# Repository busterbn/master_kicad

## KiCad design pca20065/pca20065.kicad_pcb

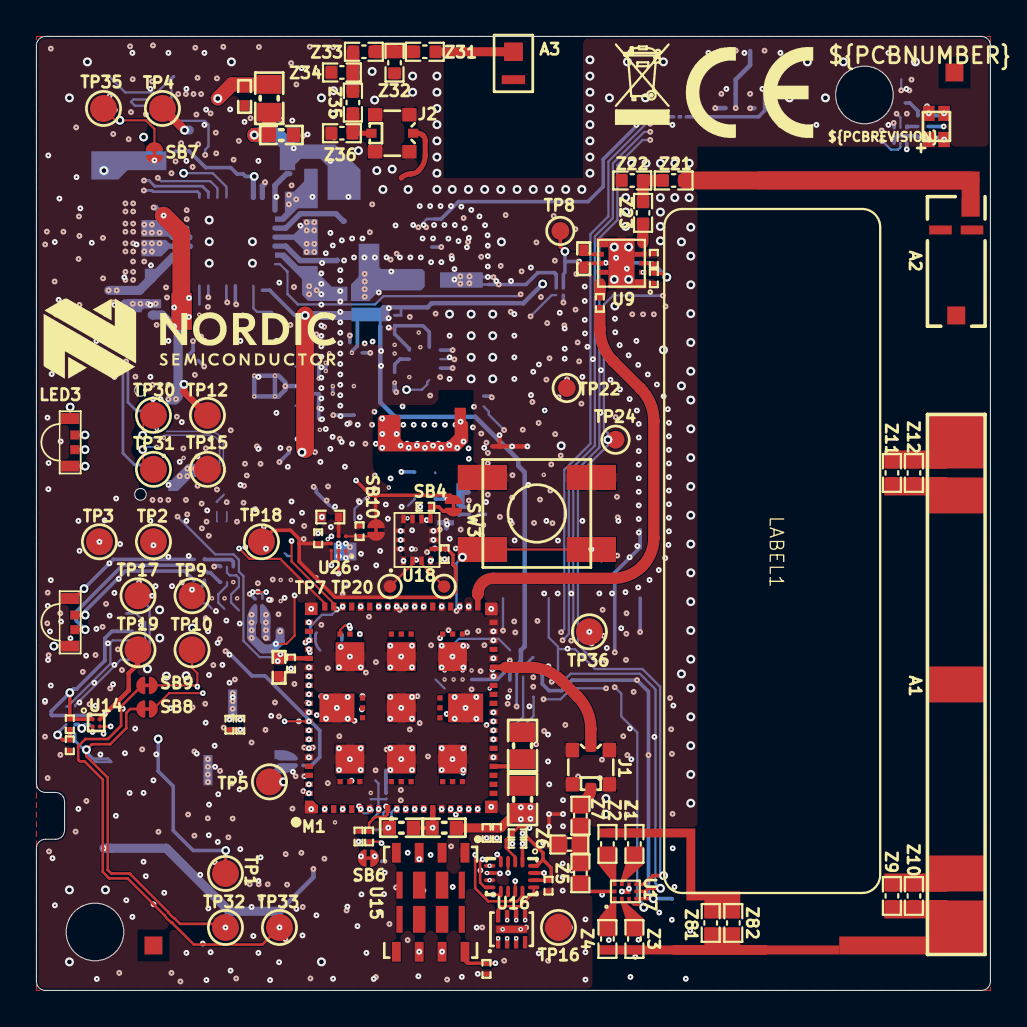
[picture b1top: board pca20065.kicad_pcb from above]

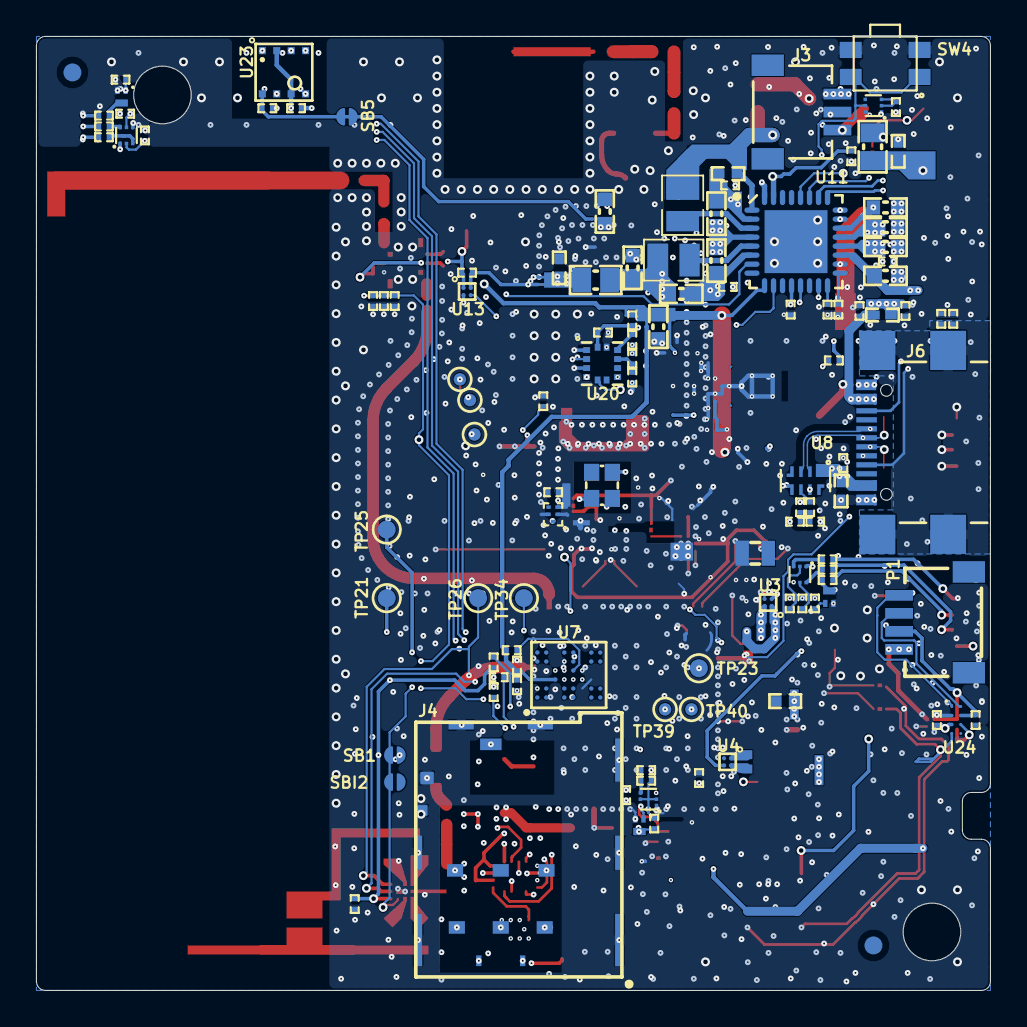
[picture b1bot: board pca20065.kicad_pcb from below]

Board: 6 copper layers, 53.0 x 53.0 mm, 230 parts (121 on the bottom side), 154 nets.

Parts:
A1: NN03-310; NN03-310_RF_ALT1
A2: NN03-320
A3: NN02-101; NN02-101_Corner
C1: 15pF; CAPC0603X03L_C
C2, C4, C7, C10, C11, C33, C34, C35, C37, C39, C40, C44, C56, C57, C75, C76, C79, C86, C87, C88, C91, C92, C93: 100nF; CAPC0603X03L_C
C3: 47µF; CAPC2012X11L
C5: 4.7µF; CAPC1005X04L
C6: 4.7µF; CAPC2012X11L
C8: 2.2µF; CAPC1005X04L_C2
C9, C58, C74: 1.0nF; CAPC0603X03L_C
C14: 1.0µF; CAPC1005X04L
C31: 39pF; CAPC0603X03L_C
C32, C36, C38: 100pF; CAPC0603X03L_C
C43, C54: 10nF; CAPC0603X03L_C
C46, C50: 1.0µF; CAPC1608X06L
C47, C48, C49, C53, C89, C90, C94, C96, C103: 10µF; CAPC1608X06L
C51: 2.2µF; CAPC1608X06L
C52: 10µF; CAPC1005X04L
C59: N.C.; CAPC0603X03L_C_NC
C95, C97, C98: 100pF; CAPC1005X04L
C99, C100, C101, C102: 10pF; CAPC0603X03L_C
CR1: EZA-EG1N50AC; RESC0603X03L_C
D3: TPD3F303DPVR; SON50P210X160X65_HS-9N
F1: SAFFB2G45MA0F0A
FB1: 120R/0.7A; INDC1608X06L
FB2: 120R/0.55A; INDC1005X04L
FB3, FB4, FB5: BLM21AG102SN1D; INDC2012X11L
Fid1, Fid2: Fiducial mark; Fiducial_Round-Square
H1, H2: MountingHole_NPTH; MountingHole_3.2_M3
J1, J2: MM8130-2600; COAXIAL-SWF
J3: HDR-3, 1mm; SM03B-SRSS-TB
J4: SF72S006VBxR2500
J6: USB-C 2.0; USB4110
L5: 9.1nH; INDC1005X04L_WW
L7, L8: 2.2µH; INDC2016X10N
LABEL1: 12x38mm; LabelSilk_12x38
LED1: LED RGB; LED_RGB_0606
LED2, LED3: LED RGB; OVSRRGBCC3_Side
LOGO1: WEE Symbol; WEE_3x4.5mm
LOGO2: Nordic Logo; NORDIC_LOGO_LYING
M1: nRF9151-LACAA1A; LGA50P1210X1110X130-113N
NT1, NT2: Net tie; 2 PIN STARPOINT
P1: HDR-4, 1mm; SM04B-SRSS-TB
Q1, Q3, Q14: RV2C010UNT2L; DFN65P100X40-3L
Q2, Q4: DMN2990UDJ; DMx299UDJ
Q6, Q13: DMC2990UDJ; DMx299UDJ
R1, R106: 10k; RESC0603X03L_C
R2, R26: 1k; RESC0603X03L_C
R3, R30, R38, R41, R42, R44, R45, R46, R49, R54: 1M0; RESC0603X03L_C
R5, R27, R28, R29, R31, R34: 0R; RESC0603X03L_C
R7: 47k; RESC0603X03L_C
R8: 330k; RESC0603X03L_C
R12, R19: 100R; RESC0603X03L_C
R13, R14, R20, R21: 39R; RESC0603X03L_C
R15: 4M7; RESC0603X03L_C
R22, R23: 4k7; RESC0603X03L_C
R24: 0.1R; RESC1005X04L
R43, R50, R53, R64, R107: 100k; RESC0603X03L_C
R56, R108: N.C.; RESC0603X03L_C_NC
SB1: Solderbridge
SB4, SB5, SB6, SB7, SB8, SB9, SB10: Solderbridge; Solderbridge_Shorted
SBI2: Solderbridge
ST1, ST2, ST3, ST4, ST5, ST7, ST9: Net tie; 2 PIN STARPOINT
SW3: PB SW; L-KLS7-TS6616B-2.5-160-T
SW4: L-KLS7-TS5401A-1.35-250-T
TP1, TP2, TP3, TP4, TP5, TP9, TP10, TP12, TP15, TP16, TP17, TP18, TP19, TP30, TP31, TP32, TP33, TP35, TP36: Ø1.5mm,SMD; TP_SMD_D1.5mm
TP6, TP7, TP20, TP37, TP38, TP39, TP40: Ø0.7mm,SMD; TP_SMD_D0.7mm
TP8, TP21, TP22, TP23, TP24, TP25, TP26, TP34: Ø1.0mm,SMD; TP_SMD_D1.0mm
U3, U4, U13, U14: TCK106AG; BGA4C40P2X2_76X76X62
U7: GD25LE255ELIG; BGA32C50P6X8_350X400X50
U8: ECMF02-4CMX8; UFDFN50P120X250X55-8N
U9: SKY65943-11
U11: nPM1300-QEAAC0; Nordic_QFN50P500X500X90-33N
U15: MFFx_M2M_UICC; SON127P600X90_HS-8N
U16: NX3DV2567; XQFN40P180X260X50-16N
U17: QM13345; PQFN40P110X150X50-10N
U18: BMI270
U20: ADXL367; LGA50P220X230X97-12N
U23: BME688; BME680
U24: TXS0102YZPR; BGA8C50P2X4_89X189X50
U26: BMM350; BGA9C40P3X3_128X128X54
X1: 32MHz; BT-XTAL_2016
X2: 32.768kHz; XTAL_2012
Z1: 6.0pF; C1608X06L-C1005X04M
Z2, Z5, Z7, Z23, Z81, Z82: 0R; C1608X06L-C1005X04M
Z3: 2.1pF; C1608X06L-C1005X04M
Z4, Z6: 3.7nH; C1608X06L-C1005X04M
Z9: 0.3pF; C1608X06L-C1005X04M
Z10: 12nH; C1608X06L-C1005X04M
Z11, Z12, Z32, Z36: N.C.; C1608X06L-C1005X04M
Z21: 2.8nH; C1608X06L-C1005X04M
Z22: 2.5nH; C1608X06L-C1005X04M
Z31: 3.8nH; C1608X06L-C1005X04M
Z33: 6.0nH; C1608X06L-C1005X04M
Z34: 0.4pF; C1608X06L-C1005X04M
Z35: 1.8pF; C1608X06L-C1005X04M

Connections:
1V8: C79.1, C95.2, FB3.2, U11.12 (VDDIO)
1V8_IND: C52.2, C94.2, FB3.1, L7.1, U11.1 (VOUT1)
1V8_SW: C4.1, C5.1, C7.1, C57.2, C75.2, C89.2, C91.2, C93.2, M1.65 (VDD_GPIO), R22.1, R23.1, R106.1, ST7.1, ST9.1, TP18.1 (1_1), U3.A2 (VIN), U11.9 (GPIO2), U11.30 (LSIN2/VINLDO2), U18.5 (VDDIO), U23.2 (CSB), U23.6 (VDDIO), U24.C1 (VccA), U26.B3 (VDDIO)
3V3: C97.2, FB4.2, ST2.1, ST3.1, TP19.1 (1_1), U14.A2 (VIN)
3V3_IND: C53.2, C96.2, FB4.1, L8.1, U11.32 (VOUT2)
/Interface/4FF_DETECT: J4.DSW, R49.1, U16.2 (IN)
/Interface/BUTTON1: M1.44 (P0.26), SW3.2 (COM), TP36.1 (1_1), U11.7 (GPIO0)
/Interface/BUTTON2: Q6.6 (D1), SB7.2 (1), TP35.1 (1_1)
/Interface/CLK: D3.2 (CLK_OUT), J4.C3 (SIMCLK)
/Interface/D:J6_N: J6.A7 (DN1), J6.B7 (DN2), TP30.1 (1_1), U8.2 (D–)
/Interface/D:J6_P: J6.A6 (DP1), J6.B6 (DP2), TP31.1 (1_1), U8.3 (D+)
/Interface/DATA: D3.3 (DATA2_OUT), J4.C7 (SIMDATA)
/Interface/EXP_BOARD.PIN1: M1.80 (P0.19), SB9.1 (0), TP33.1 (1_1), U24.D2 (A1)
/Interface/EXP_BOARD.PIN2: M1.79 (P0.18), SB8.1 (0), TP32.1 (1_1), U24.D1 (A2)
/Interface/I2C.SCL: M1.67 (P0.08), R22.2, SB8.2 (1), TP9.1 (1_1), U11.14 (SCL), U20.4 (~CS/SCL), U23.4 (SCK), U26.A3 (SCK)
/Interface/I2C.SDA: M1.68 (P0.09), R23.2, SB9.2 (1), TP10.1 (1_1), U11.13 (SDA), U20.2 (MOSI/SDA), U23.3 (SDI), U26.A2 (SDA)
/Interface/IF_SWD.RST: Q13.2 (G1), Q13.5 (G2), R107.1, R108.1
/Interface/LOAD_SW_DISABLE: R3.1, TP1.1 (1_1), U3.B2 (CTRL), U4.B2 (CTRL)
/Interface/NX_COM.CH1: C34.2, M1.19 (SIM_1V8), R49.2, U16.14 (VCC), U16.16 (COM1)
/Interface/NX_COM.CH2: M1.17 (SIM_IO), U16.4 (COM2)
/Interface/NX_COM.CH3: M1.18 (SIM_CLK), U16.8 (COM3)
/Interface/NX_COM.CH4: M1.16 (SIM_RST), U16.12 (COM4)
/Interface/NX_NC.CH1: C54.1, D3.5 (VCC), J4.C1 (VSIM), U16.1 (NC1)
/Interface/NX_NC.CH2: D3.6 (DATA2_IN), U16.5 (NC2)
/Interface/NX_NC.CH3: D3.7 (CLK_IN), U16.9 (NC3)
/Interface/NX_NC.CH4: D3.8 (DATA1_IN), U16.13 (NC4)
/Interface/NX_NO.CH1: C59.2, U15.8 (SIMVCC), U16.15 (NO1)
/Interface/NX_NO.CH2: U15.3 (SIMDATA), U16.3 (NO2)
/Interface/NX_NO.CH3: U15.6 (SIMCLK), U16.7 (NO3)
/Interface/NX_NO.CH4: U15.7 (SIMRST), U16.11 (NO4)
/Interface/PMIC_CC.CC1: J6.A5 (CC1), U11.23 (CC1)
/Interface/PMIC_CC.CC2: J6.B5 (CC2), U11.24 (CC2)
/Interface/RST: D3.1 (DATA1_OUT), J4.C2 (SIMRST)
/Interface/USB.D_N: C99.1, R31.1
/Interface/USB.D_P: C100.1, R34.1
/Interface/nRF54_SWD.RST: SB6.2 (1), TP5.1 (1_1)
/Power_Supply/EXP_BRD_CTRL: M1.59 (P0.03), U14.B2 (CTRL)
/Power_Supply/INTERRUPT.INT1: M1.58 (P0.02), U11.10 (GPIO3)
/Power_Supply/INTERRUPT.INT2: M1.63 (P0.06), U18.4 (INT1)
/Power_Supply/INTERRUPT.INT3: M1.64 (P0.07), U26.A1 (INT)
/Power_Supply/INTERRUPT.INT4: M1.70 (P0.11), U20.5 (INT1)
/Power_Supply/LD3_B: LED3.3 (C_BLUE), U11.27 (LED2)
/Power_Supply/LD3_G: LED3.2 (C_GREEN), U11.26 (LED1)
/Power_Supply/LD3_R: LED3.1 (C_RED), U11.25 (LED0)
/Power_Supply/NTC: J3.2, U11.18 (NTC)
/Power_Supply/SHPHLD: Q6.5 (G2), SW4.1 (N.O), U11.15 (SHPHLD)
/Power_Supply/SW1: L7.2, U11.3 (SW1)
/Power_Supply/SW2: L8.2, U11.5 (SW2)
/Power_Supply/VSET1: R7.1, U11.17 (VSET1)
/Power_Supply/VSET2: R8.1, U11.16 (VSET2)
/RF_Frontend/BLE_RF: CR1.2, F1.4 (OUT)
/RF_Frontend/GPS_RF: U9.5 (RF_IN), Z23.1
/RF_Frontend/ID: SB1.2 (1), SBI2.1 (0), TP25.1 (1_1), U17.3 (ID)
/RF_Frontend/LTE_RF: J1.1 (IN), M1.35 (ANT)
/RF_Frontend/RF1: U17.2 (RF1), Z3.1
/RF_Frontend/RF2: U17.8 (RF2), Z1.1
/RF_Frontend/RF3: U17.9 (RF3), Z2.1
/RF_Frontend/RF4: U17.1 (RF4), Z4.1
/RF_Frontend/RFC: U17.10 (RFC), Z5.2
/RF_Frontend/RFFE.SCLK: M1.28 (SCLK), R28.1
/RF_Frontend/RFFE.SDATA: M1.27 (SDATA), R27.1
/RF_Frontend/RFFE.VIO: M1.29 (VIO), R29.1
/RF_Frontend/SCLK: R28.2, TP26.1 (1_1), U17.6 (SCLK)
/RF_Frontend/SDATA: R27.2, TP34.1 (1_1), U17.5 (SDATA)
/RF_Frontend/VIO: C38.2, R29.2, SB1.1 (0), TP21.1 (1_1), U17.4 (VIO)
/Sensors_LEDs/ASCL: TP20.1 (1_1), U18.3 (ASCx)
/Sensors_LEDs/ASDA: TP7.1 (1_1), U18.2 (ASDx)
/Sensors_LEDs/FLASH.~CS: M1.72 (P0.12), U7.C4 (~CS)
/Sensors_LEDs/FLASH.~RESET: R50.1, U7.D3 (IO3/~HLD/~RST)
/Sensors_LEDs/FLASH.~WP: R43.1, U7.E4 (IO2/~WP)
/Sensors_LEDs/LD1_B: LED1.3 (C_BLUE), R14.2
/Sensors_LEDs/LD1_G: LED1.2 (C_GREEN), R13.2
/Sensors_LEDs/LD1_R: LED1.1 (C_RED), R12.2
/Sensors_LEDs/LD2_B: LED2.3 (C_BLUE), R21.2
/Sensors_LEDs/LD2_G: LED2.2 (C_GREEN), R20.2
/Sensors_LEDs/LD2_R: LED2.1 (C_RED), R19.2
/Sensors_LEDs/LED2.BLUE: Q2.5 (G2), R42.2
/Sensors_LEDs/LED2.GREEN: Q1.1 (G), R41.2
/Sensors_LEDs/LED2.RED: Q2.2 (G1), R38.2
/Sensors_LEDs/LED.BLUE: M1.49 (P0.30), Q4.5 (G2), R46.2
/Sensors_LEDs/LED.GREEN: M1.50 (P0.31), Q4.2 (G1), R45.2
/Sensors_LEDs/LED.RED: M1.48 (P0.29), Q3.1 (G), R44.2
/Sensors_LEDs/SPI.MISO: M1.75 (P0.15), TP6.1 (1_1), U7.D4 (IO1/SO), U18.1 (SDO)
/Sensors_LEDs/SPI.MOSI: M1.74 (P0.14), TP37.1 (1_1), U7.F3 (IO0/SI), U18.14 (SDx)
/Sensors_LEDs/SPI.SCK: M1.73 (P0.13), TP38.1 (1_1), U7.E3 (SCLK), U18.13 (SCx)
/nRF54L15/BMI270_CS: M1.69 (P0.10), U18.12 (CSB)
/nRF54L15/LTE_BLE_COEX: M1.54 (COEX2), R53.2, TP22.1 (1_1), U13.B2 (CTRL)
/nRF9151/DEC0: C6.1, M1.24 (DEC0)
/nRF9151/GPS_EN: C35.2, C36.2, M1.52 (COEX0), R54.2, TP24.1 (1_1), U9.2 (VEN)
/nRF9151/GPS_RF1: C31.2, M1.42 (GPS)
/nRF9151/GPS_RF2: C31.1, U9.10 (RF_OUT)
GND: C1.2, C2.2, C3.2, C4.2, C5.2, C6.2, C7.2, C8.1, C10.2 (2_2), C11.1, C14.1, C32.1, C33.1, C34.1, C35.1, C36.1, C37.1, C38.1, C39.1, C40.1, C43.1, C44.1, C46.1, C49.1, C50.1, C51.1, C54.2, C56.1, C57.1, C58.1, C59.1, C75.1, C76.1, C79.2, C86.1, C87.1, C88.1, C89.1, C90.1, C91.1, C92.1, C93.1, C94.1, C95.1, C96.1, C97.1, C98.1, C99.2, C100.2, C101.1, C102.1, C103.1, CR1.1, D3.9 (GND), F1.2 (GND), F1.3 (GND), F1.5 (GND), J1.2 (Shield), J2.2 (Shield), J3.1, J4.0 (GND), J4.C5 (GND), J4.CSW, J6.A1 (GND), J6.A12 (GND), M1.1 (GND), M1.7 (GND), M1.13 (GND), M1.15 (GND), M1.20 (GND), M1.25 (GND), M1.30 (GND), M1.34 (GND), M1.36 (GND), M1.38 (GND), M1.39 (GND), M1.40 (GND), M1.41 (GND), M1.43 (GND), M1.46 (GND), M1.51 (GND), M1.55 (GND), M1.60 (GND), M1.66 (GND), M1.71 (GND), M1.76 (GND), M1.105 (GND), M1.106 (GND), M1.107 (GND), M1.108 (GND), M1.109 (GND), M1.110 (GND), M1.111 (GND), M1.112 (GND), M1.113 (GND), NT1.1, NT2.1, P1.1, Q1.2 (S), Q2.1 (S1), Q2.4 (S2), Q3.2 (S), Q4.1 (S1), Q4.4 (S2), Q6.1 (S1), Q13.1 (S1), Q14.2 (S), R7.2, R8.2, R15.2 (2_2), R30.1, R38.1, R41.1, R42.1, R44.1, R45.1, R46.1, R53.1, R54.1, R64.2, SBI2.2 (1), SW3.1 (N.O), SW4.2 (COM), TP15.1 (1_1), TP16.1 (1_1), U3.B1 (GND), U4.B1 (GND), U7.A2 (NC), U7.D5 (NC), U7.F4 (VSS), U8.5 (GND), U8.8 (GND), U9.1 (GND), U9.4 (GND), U9.6 (GND), U9.9 (GND), U9.11 (GND), U11.33 (AVSS), U13.B1 (GND), U14.B1 (GND), U15.1 (GND), U16.6 (GND), U17.7 (GND), U18.6 (GNDIO), U18.7 (GND), U20.1 (SCLK), U20.3 (MISO/ASEL), U20.7 (GND), U20.11 (GND), U23.1 (GND), U23.5 (SDO), U23.7 (GND), U24.B1 (GND), U26.B1 (GND), U26.B2 (ADSEL), U26.C3 (BYPASS), X1.2 (GND), X1.4 (GND), Z6.2, Z22.2, Z32.1, Z34.2, Z36.2
unnamed: A1.1 (Feed), Z3.2, Z4.2, Z9.1, Z10.1, Z81.2, Z82.2
unnamed: A1.2 (Tuning), Z9.2, Z10.2
unnamed: A1.3 (Tuning), Z11.2, Z12.2
unnamed: A1.4 (Tuning), Z11.1, Z12.1
unnamed: A2.4 (Feed1_4), Z21.2
unnamed: A3.1 (1_1), Z31.2
unnamed: J1.3 (OUT), Z7.1
unnamed: J2.3 (OUT), Z35.1, Z36.1
unnamed: C103.2, FB1.2, M1.14 (VDD), R1.1 (1_1)
unnamed: M1.2 (P0.20), SB6.1 (0)
unnamed: M1.53 (COEX1), TP23.1 (1_1)
unnamed: M1.99 (RESERVED), TP39.1 (1_1)
unnamed: M1.101 (RESERVED), TP40.1 (1_1)
unnamed: Q1.3 (D), R20.1
unnamed: Q2.6 (D1), R19.1
unnamed: Q2.3 (D2), R21.1
unnamed: Q3.3 (D), R12.1
unnamed: Q4.6 (D1), R13.1
unnamed: Q4.3 (D2), R14.1
unnamed: Q6.2 (G1), Q6.3 (D2), R64.1
unnamed: Q13.3 (D2), Q13.6 (D1), Q14.1 (G)
unnamed: Q13.4 (S2), R106.2, R107.2
unnamed: Q14.3 (D), R2.1 (1_1), R108.2
unnamed: R31.2, U8.7 (D–)
unnamed: R34.2, U8.6 (D+)
unnamed: C39.2, SB4.2 (1), U18.8 (VDD)
unnamed: C56.2, SB5.2 (1), U23.8 (VDD)
unnamed: C92.2, SB10.2 (1), U26.C1 (VDD)
unnamed: L5.2 (2_2), U9.7 (FIL_OUT)
unnamed: C9.2, C47.2, C48.2, C49.2, C58.2, C74.2, FB5.1, U11.4 (PVDD), U11.20 (VSYS)
unnamed: C87.2, C88.2, R26.2, U20.10 (VS), U20.12 (VDDIO)
unnamed: C40.2, C86.2, U20.9 (VREG_OUT)
unnamed: P1.3, U24.A2 (B1)
unnamed: P1.4, U24.A1 (B2)
unnamed: C8.2, U26.C2 (CRST)
unnamed: Z1.2, Z2.2, Z81.1, Z82.1
unnamed: Z5.1, Z6.1, Z7.2
unnamed: Z21.1, Z22.1, Z23.2
unnamed: Z31.1, Z32.2, Z33.2
unnamed: Z33.1, Z34.1, Z35.2
PVSS1: C9.1, C47.1, C52.1, NT1.2, U11.2 (PVSS1)
PVSS2: C48.1, C53.1, C74.1, NT2.2, U11.6 (PVSS2)
Shield: C101.2, C102.2, J6.SHLD (SHELL)
VBAT: C51.2, J3.3, TP4.1 (1_1), U11.19 (VBAT)
VBUS: C44.2, C46.2, FB2.2, U11.21 (VBUS)
VBUSOUT: C50.2, U11.22 (VBUSOUT)
VBUS_CONN: C11.2, C14.2, C43.2, FB2.1, J6.A4 (VBUS), J6.A9 (VBUS), TP12.1 (1_1), U8.1 (VBUS)
VDD_ACC: R26.1, ST7.2
VDD_BMI270: SB4.1 (0), ST1.2
VDD_BMM350: SB10.1 (0), ST4.2
VDD_ENV: SB5.1 (0), ST5.2
VDD_EXP_BRD: C76.2, P1.2, R5.1 (1_1), U14.A1 (VOUT), U24.B2 (VccB)
VDD_LED: LED1.4 (A), LED2.4 (A), ST2.2
VDD_MEM: C37.2, R43.2, R50.2, ST9.2, U7.C3 (VCC)
VDD_RF_FE_3V3: C32.2, C33.2, R56.1, TP8.1 (1_1), U9.3 (VCC), U13.A1 (VOUT)
VDD_RF_FE_3V3_SP: R56.2, ST3.2, U13.A2 (VIN)
VDD_SENS: C90.2, R30.2, ST1.1, ST4.1, ST5.1, U11.31 (LSOUT2/VOUTLDO2)
VDD_nRF54: TP2.1 (1_1), U3.A1 (VOUT)
VDD_nRF91: C1.1, C2.1, C3.1, FB1.1, TP3.1 (1_1), U4.A1 (VOUT)
VDD_nRF91_RES: R24.1, U4.A2 (VIN)
VSYS: C98.2, FB5.2, LED3.4 (A), Q6.4 (S2)
VSYS_SW: R3.2, R24.2, TP17.1 (1_1), U11.28 (LSIN1/VINLDO1)
